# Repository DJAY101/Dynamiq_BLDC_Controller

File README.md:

# A simple Brushless Motor Controller

I'm currently on the journey of creating a simple cost effective controller that
will eventually be sold to the masses to remove the high barrier to entry into using high performing brushless motor actuators.

FRC Falcon 500 Motors inspired this project, since there are no suitable motor options at a suitable price that enables hobbyists to utilise these amazing pieces of technology. (Odrive being 200USD+)

# This project is still in its very early stages...
(Do note this is actually my very second PCB designed, so I lack a lot of experience)

Version 1 of the PCB worked with the following code. However I ended up frying two of the boards during programming and tinkering with the board. I am currently working on a version 2 iteration of the PCB from the mistakes and lack of safety features in V1. 

(I actually got the motor to turn on the very first iteration of this board which is a massive win)

## Failures so far...
- Somehow killed the TMC6200 gate driver while I was tinkering with the code. it does not like being fed a PWM duty cycle of greater than 40%
- Magic smoke occured on my buck converter where 4s Lipo is converted to 5V. Still unsure what happened here, but I have a few hypothesis. Sketchy soldering on my ESP32 3.3v and ground pin causing a short. Or accidentally shorting the the SPI clock pin with ground while unplugging the jumpers.
- The board does heat up, perhaps 2oZ layers may be needed (opted out since it was expensive for iter1)
- Practically no protection circuitry at all, except for the built in ones in the gate driver

# Improvements Underway
The progress on the code is halted as I have no working boards anymore since I fried all 2 of them haha.
- Integrate reverse polarity protection with a MOSFET Diode*
- Remove the chunky header pin and replace it with smaller header pins that connect to encoders and etc
- Initial inrush current limit to stop the spark when I connect my lipo to the board
- Fuses... Fuses and more fuses
- Change my LDO to a newer IC for more efficiency
- Capacitors on the phase output?
- Current sensing was not tested before the boards fried themselves ( caps on current sens outputs for a better averages value?)

# Other Unstructured Yap
PCB was manufactured by JLPCB, assembly services was also opted, 5 boards were 10 bucks aud and assembly and parts for 2 board added $150 aud

Reddit also reviewd my board before I manufactured it heres the link to that discussion
https://www.reddit.com/r/PCB/comments/1lk1n3d/review_request_my_first_pcb_bldc_sinusoidal/

This man made coding this thing a lot easier. Just pass sine waves into the motor and itll turn. I reckon it was much more easier to implement than step control.
https://www.youtube.com/watch?v=zSdetJsSeNw&t

Cool channels
- https://www.youtube.com/watch?v=mbJOxqxLkLE
- https://www.youtube.com/watch?v=e0sQnVmE7DU

If you'd like to contact me for more information or collaboration on this project feel free to DM me on insta at DJAY10101, or if you prefer email its djay01602@gmail.com

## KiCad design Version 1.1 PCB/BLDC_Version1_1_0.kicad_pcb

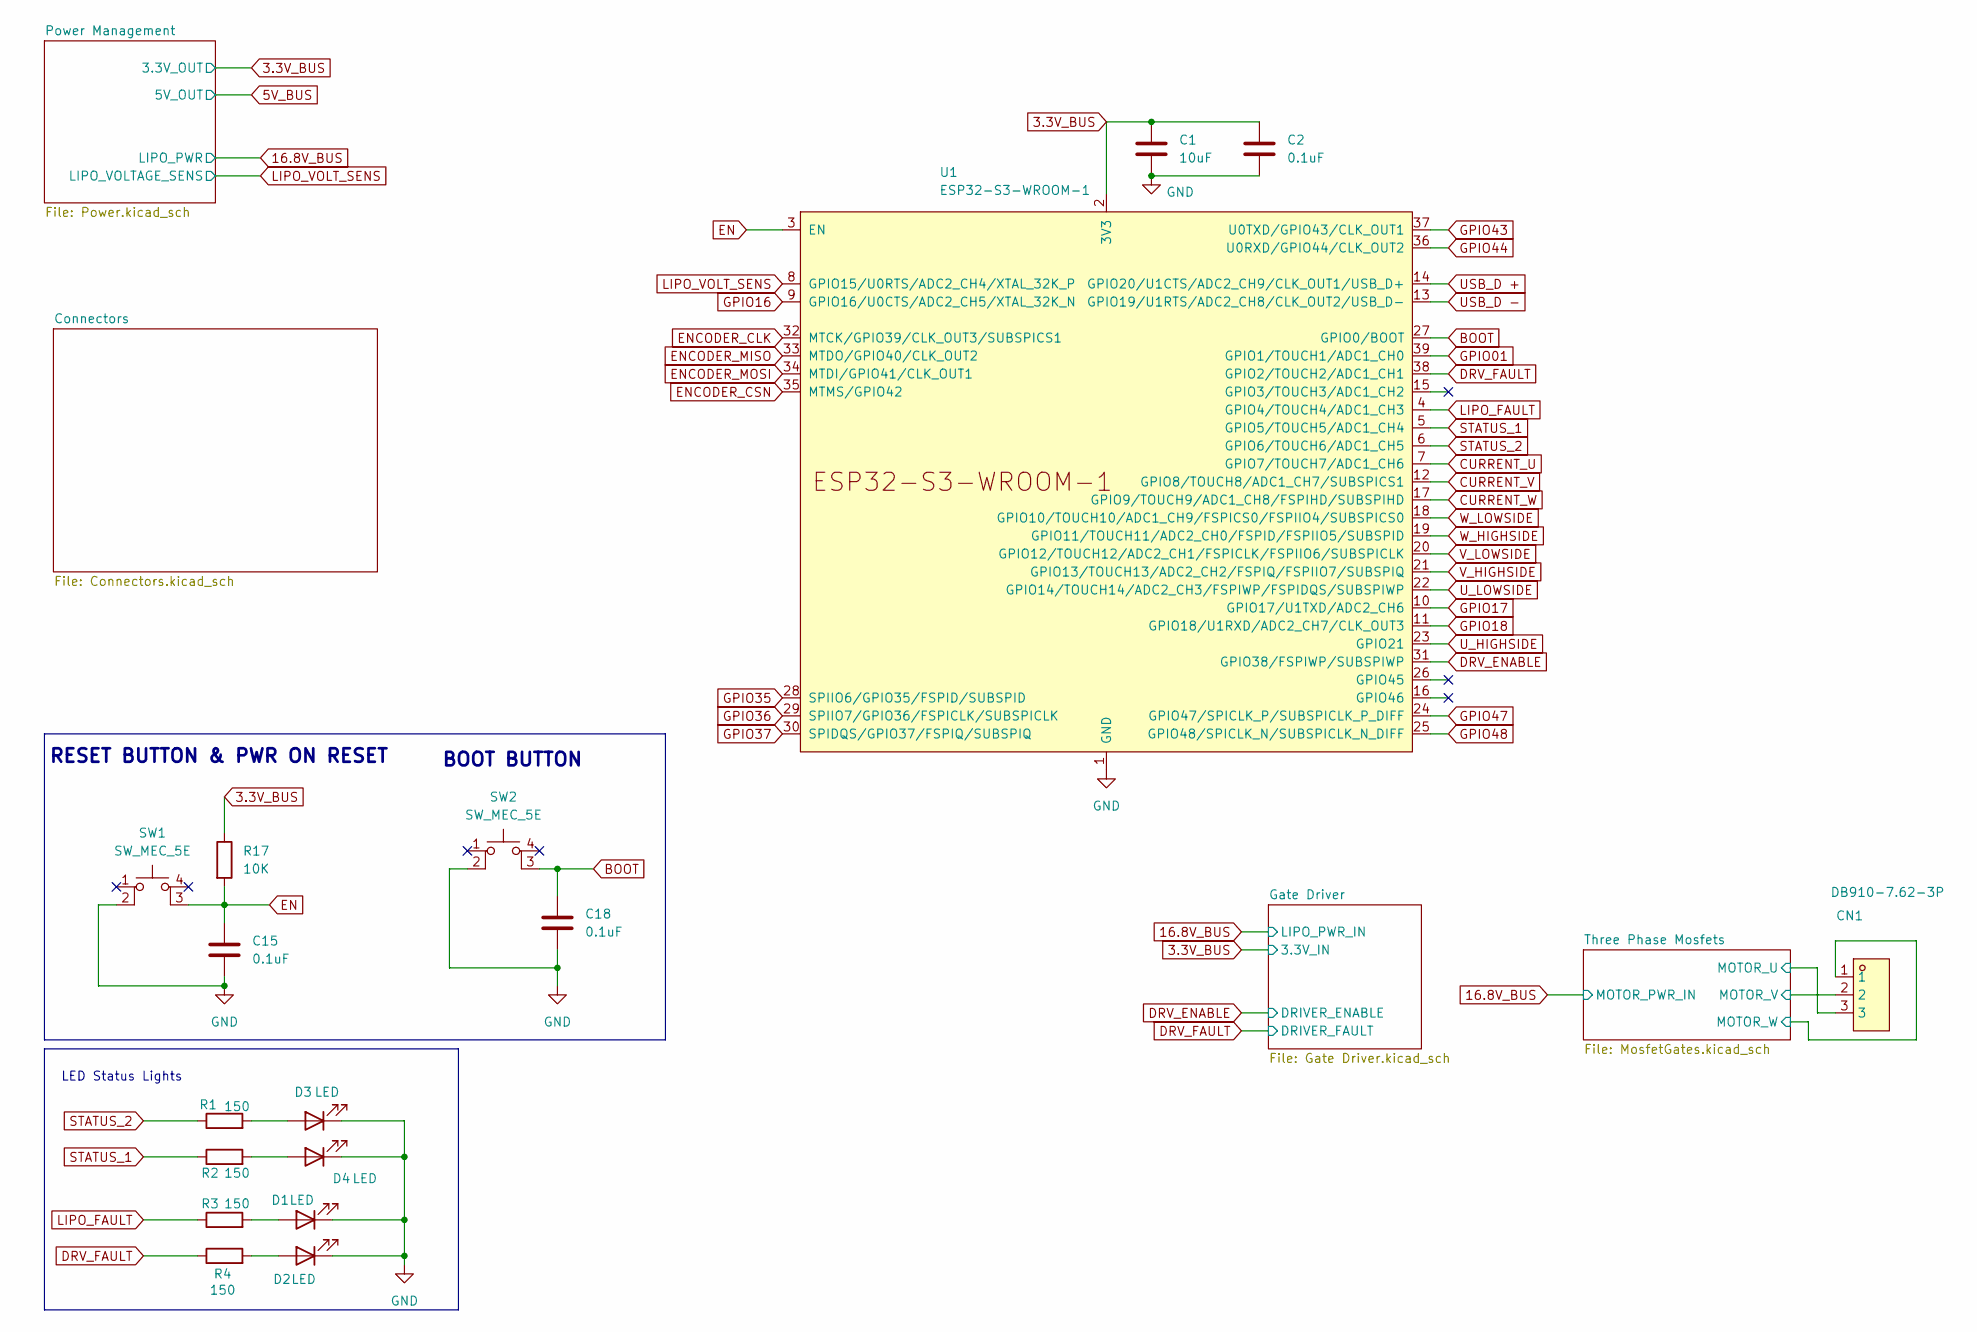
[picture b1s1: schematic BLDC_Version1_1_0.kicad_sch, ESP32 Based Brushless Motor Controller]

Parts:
C1: 10uF; C_0805_2012Metric_Pad1.18x1.45mm_HandSolder
C2, C15, C18: 0.1uF; C_0805_2012Metric_Pad1.18x1.45mm_HandSolder
CN1: DB910-7.62-3P; CONN-TH_3P-P7.62_DB910-7.62-3P; LCSC Part C395877
D1, D2: LED; LED_0603_1608Metric_Pad1.05x0.95mm_HandSolder
D3, D4: LED; LED_0805_2012Metric_Pad1.15x1.40mm_HandSolder
R1, R2, R3, R4: 150; R_0805_2012Metric_Pad1.20x1.40mm_HandSolder
R17: 10K; R_0805_2012Metric_Pad1.20x1.40mm_HandSolder
SW1, SW2: SW_MEC_5E; SW-SMD_4P-L5.2-W5.2-P3.70-LS6.5
U1: ESP32-S3-WROOM-1

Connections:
3.3V_BUS: C1.1, C2.1, R17.1, U1.2 (3V3); also elsewhere on the board
BOOT: C18.1, SW2.3 (K), U1.27 (GPIO0/BOOT)
CURRENT_U: U1.7 (GPIO7/TOUCH7/ADC1_CH6); also elsewhere on the board
CURRENT_V: U1.12 (GPIO8/TOUCH8/ADC1_CH7/SUBSPICS1); also elsewhere on the board
CURRENT_W: U1.17 (GPIO9/TOUCH9/ADC1_CH8/FSPIHD/SUBSPIHD); also elsewhere on the board
DRV_ENABLE: U1.31 (GPIO38/FSPIWP/SUBSPIWP); also elsewhere on the board
DRV_FAULT: R4.1, U1.38 (GPIO2/TOUCH2/ADC1_CH1); also elsewhere on the board
EN: C15.1, R17.2, SW1.3 (K), U1.3 (EN)
ENCODER_CLK: U1.32 (MTCK/GPIO39/CLK_OUT3/SUBSPICS1); also elsewhere on the board
ENCODER_CSN: U1.35 (MTMS/GPIO42); also elsewhere on the board
ENCODER_MISO: U1.33 (MTDO/GPIO40/CLK_OUT2); also elsewhere on the board
ENCODER_MOSI: U1.34 (MTDI/GPIO41/CLK_OUT1); also elsewhere on the board
GND: C1.2, C2.2, C15.2, C18.2, D1.1 (K), D2.1 (K), D3.1 (K), D4.1 (K), SW1.2, SW2.2, U1.1 (GND), U1.40 (GND), U1.41 (GND); also elsewhere on the board
GPIO01: U1.39 (GPIO1/TOUCH1/ADC1_CH0); also elsewhere on the board
GPIO16: U1.9 (GPIO16/U0CTS/ADC2_CH5/XTAL_32K_N); also elsewhere on the board
GPIO17: U1.10 (GPIO17/U1TXD/ADC2_CH6); also elsewhere on the board
GPIO18: U1.11 (GPIO18/U1RXD/ADC2_CH7/CLK_OUT3); also elsewhere on the board
GPIO35: U1.28 (SPIIO6/GPIO35/FSPID/SUBSPID); also elsewhere on the board
GPIO36: U1.29 (SPIIO7/GPIO36/FSPICLK/SUBSPICLK); also elsewhere on the board
GPIO37: U1.30 (SPIDQS/GPIO37/FSPIQ/SUBSPIQ); also elsewhere on the board
GPIO43: U1.37 (U0TXD/GPIO43/CLK_OUT1); also elsewhere on the board
GPIO44: U1.36 (U0RXD/GPIO44/CLK_OUT2); also elsewhere on the board
GPIO47: U1.24 (GPIO47/SPICLK_P/SUBSPICLK_P_DIFF); also elsewhere on the board
GPIO48: U1.25 (GPIO48/SPICLK_N/SUBSPICLK_N_DIFF); also elsewhere on the board
LIPO_FAULT: R3.1, U1.4 (GPIO4/TOUCH4/ADC1_CH3)
LIPO_VOLT_SENS: U1.8 (GPIO15/U0RTS/ADC2_CH4/XTAL_32K_P); also elsewhere on the board
unnamed: D1.2 (A), R3.2
unnamed: D2.2 (A), R4.2
unnamed: D3.2 (A), R1.2
unnamed: D4.2 (A), R2.2
STATUS_1: R2.1, U1.5 (GPIO5/TOUCH5/ADC1_CH4)
STATUS_2: R1.1, U1.6 (GPIO6/TOUCH6/ADC1_CH5)
U_HIGHSIDE: U1.23 (GPIO21); also elsewhere on the board
U_LOWSIDE: U1.22 (GPIO14/TOUCH14/ADC2_CH3/FSPIWP/FSPIDQS/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); also elsewhere on the board
U_SENSE: CN1.3; also elsewhere on the board
V_HIGHSIDE: U1.21 (GPIO13/TOUCH13/ADC2_CH2/FSPIQ/FSPIIO7/S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); also elsewhere on the board
V_LOWSIDE: U1.20 (GPIO12/TOUCH12/ADC2_CH1/FSPICLK/FSPIIO6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); also elsewhere on the board
V_SENSE: CN1.2; also elsewhere on the board
W_HIGHSIDE: U1.19 (GPIO11/TOUCH11/ADC2_CH0/FSPID/FSPIIO5/S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); also elsewhere on the board
W_LOWSIDE: U1.18 (GPIO10/TOUCH10/ADC1_CH9/FSPICS0/FSPIIO4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); also elsewhere on the board
W_SENSE: CN1.1; also elsewhere on the board

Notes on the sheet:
RESET BUTTON & PWR ON RESET
BOOT BUTTON
LED Status Lights

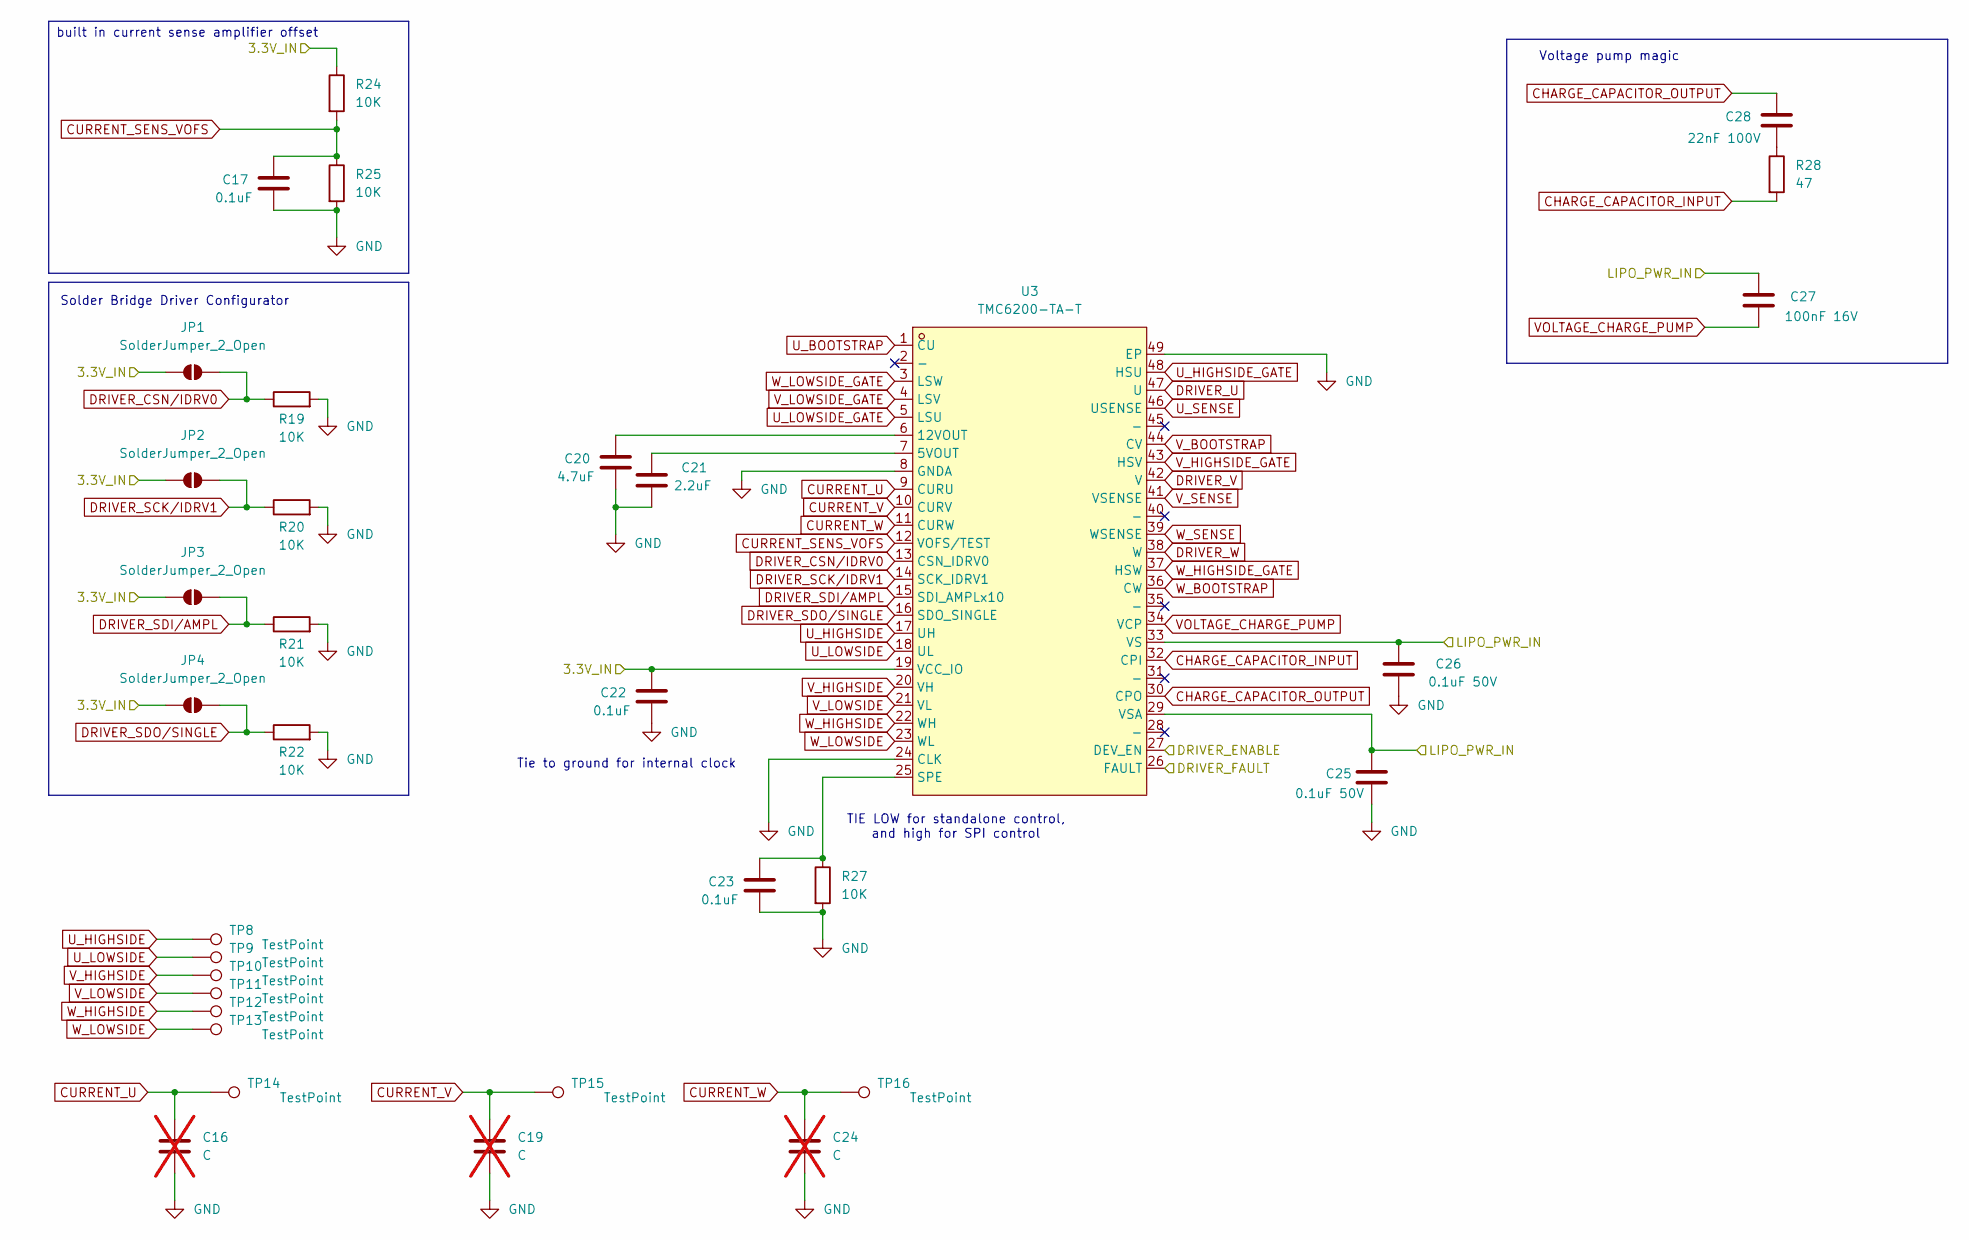
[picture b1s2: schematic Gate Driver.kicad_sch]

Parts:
C16, C19, C24: C; C_0805_2012Metric_Pad1.18x1.45mm_HandSolder; not fitted
C17, C22, C23: 0.1uF; C_0805_2012Metric_Pad1.18x1.45mm_HandSolder
C20: 4.7uF; C_0805_2012Metric_Pad1.18x1.45mm_HandSolder
C21: 2.2uF; C_0805_2012Metric_Pad1.18x1.45mm_HandSolder
C25, C26: 0.1uF 50V; C_0805_2012Metric_Pad1.18x1.45mm_HandSolder
C27: 100nF 16V; C_0805_2012Metric_Pad1.18x1.45mm_HandSolder
C28: 22nF 100V; C_0805_2012Metric_Pad1.18x1.45mm_HandSolder
JP1, JP2, JP3, JP4: SolderJumper_2_Open; SolderJumper-2_P1.3mm_Open_TrianglePad1.0x1.5mm
R19, R20, R21, R22, R24, R25, R27: 10K; R_0805_2012Metric_Pad1.20x1.40mm_HandSolder
R28: 47; R_0805_2012Metric_Pad1.20x1.40mm_HandSolder
TP8, TP9, TP10, TP11, TP12, TP13: TestPoint; TestPoint_Pad_D2.0mm
TP14, TP15, TP16: TestPoint; SMD_RH-5015
U3: TMC6200-TA-T; TQFP-48_L7.0-W7.0-P0.50-LS9.0-BL-EP; LCSC Part C465958

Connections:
3.3V_BUS: C22.1, JP1.1 (A), JP2.1 (A), JP3.1 (A), JP4.1 (A), R24.1, U3.19 (VCC_IO); also elsewhere on the board
16.8V_BUS: C25.1, C26.1, C27.1, U3.29 (VSA), U3.33 (VS); also elsewhere on the board
CHARGE_CAPACITOR_INPUT: R28.2, U3.32 (CPI)
CHARGE_CAPACITOR_OUTPUT: C28.1, U3.30 (CPO)
CURRENT_SENS_VOFS: C17.1, R24.2, R25.1, U3.12 (VOFS/TEST)
CURRENT_U: C16.1, TP14.1, U3.9 (CURU); also elsewhere on the board
CURRENT_V: C19.1, TP15.1, U3.10 (CURV); also elsewhere on the board
CURRENT_W: C24.1, TP16.1, U3.11 (CURW); also elsewhere on the board
DRIVER_CSN/IDRV0: JP1.2 (B), R19.1, U3.13 (CSN_IDRV0); also elsewhere on the board
DRIVER_SCK/IDRV1: JP2.2 (B), R20.1, U3.14 (SCK_IDRV1); also elsewhere on the board
DRIVER_SDI/AMPL: JP3.2 (B), R21.1, U3.15 (SDI_AMPLx10); also elsewhere on the board
DRIVER_SDO/SINGLE: JP4.2 (B), R22.1, U3.16 (SDO_SINGLE); also elsewhere on the board
DRIVER_U: U3.47 (U); also elsewhere on the board
DRIVER_V: U3.42 (V); also elsewhere on the board
DRIVER_W: U3.38 (W); also elsewhere on the board
DRV_ENABLE: U3.27 (DEV_EN); also elsewhere on the board
DRV_FAULT: U3.26 (FAULT); also elsewhere on the board
GND: C16.2, C17.2, C19.2, C20.2, C21.2, C22.2, C23.2, C24.2, C25.2, C26.2, R19.2, R20.2, R21.2, R22.2, R25.2, R27.2, U3.8 (GNDA), U3.24 (CLK), U3.49 (EP); also elsewhere on the board
unnamed: C28.2, R28.1
unnamed: C21.1, U3.7 (5VOUT)
unnamed: C20.1, U3.6 (12VOUT)
unnamed: C23.1, R27.1, U3.25 (SPE)
U_BOOTSTRAP: U3.1 (CU); also elsewhere on the board
U_HIGHSIDE: TP8.1, U3.17 (UH); also elsewhere on the board
U_HIGHSIDE_GATE: U3.48 (HSU); also elsewhere on the board
U_LOWSIDE: TP9.1, U3.18 (UL); also elsewhere on the board
U_LOWSIDE_GATE: U3.5 (LSU); also elsewhere on the board
U_SENSE: U3.46 (USENSE); also elsewhere on the board
VOLTAGE_CHARGE_PUMP: C27.2, U3.34 (VCP)
V_BOOTSTRAP: U3.44 (CV); also elsewhere on the board
V_HIGHSIDE: TP10.1, U3.20 (VH); also elsewhere on the board
V_HIGHSIDE_GATE: U3.43 (HSV); also elsewhere on the board
V_LOWSIDE: TP11.1, U3.21 (VL); also elsewhere on the board
V_LOWSIDE_GATE: U3.4 (LSV); also elsewhere on the board
V_SENSE: U3.41 (VSENSE); also elsewhere on the board
W_BOOTSTRAP: U3.36 (CW); also elsewhere on the board
W_HIGHSIDE: TP12.1, U3.22 (WH); also elsewhere on the board
W_HIGHSIDE_GATE: U3.37 (HSW); also elsewhere on the board
W_LOWSIDE: TP13.1, U3.23 (WL); also elsewhere on the board
W_LOWSIDE_GATE: U3.3 (LSW); also elsewhere on the board
W_SENSE: U3.39 (WSENSE); also elsewhere on the board

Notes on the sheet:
built in current sense amplifier offset
Voltage pump magic
Tie to ground for internal clock
Solder Bridge Driver Configurator
TIE LOW for standalone control, and high for SPI control

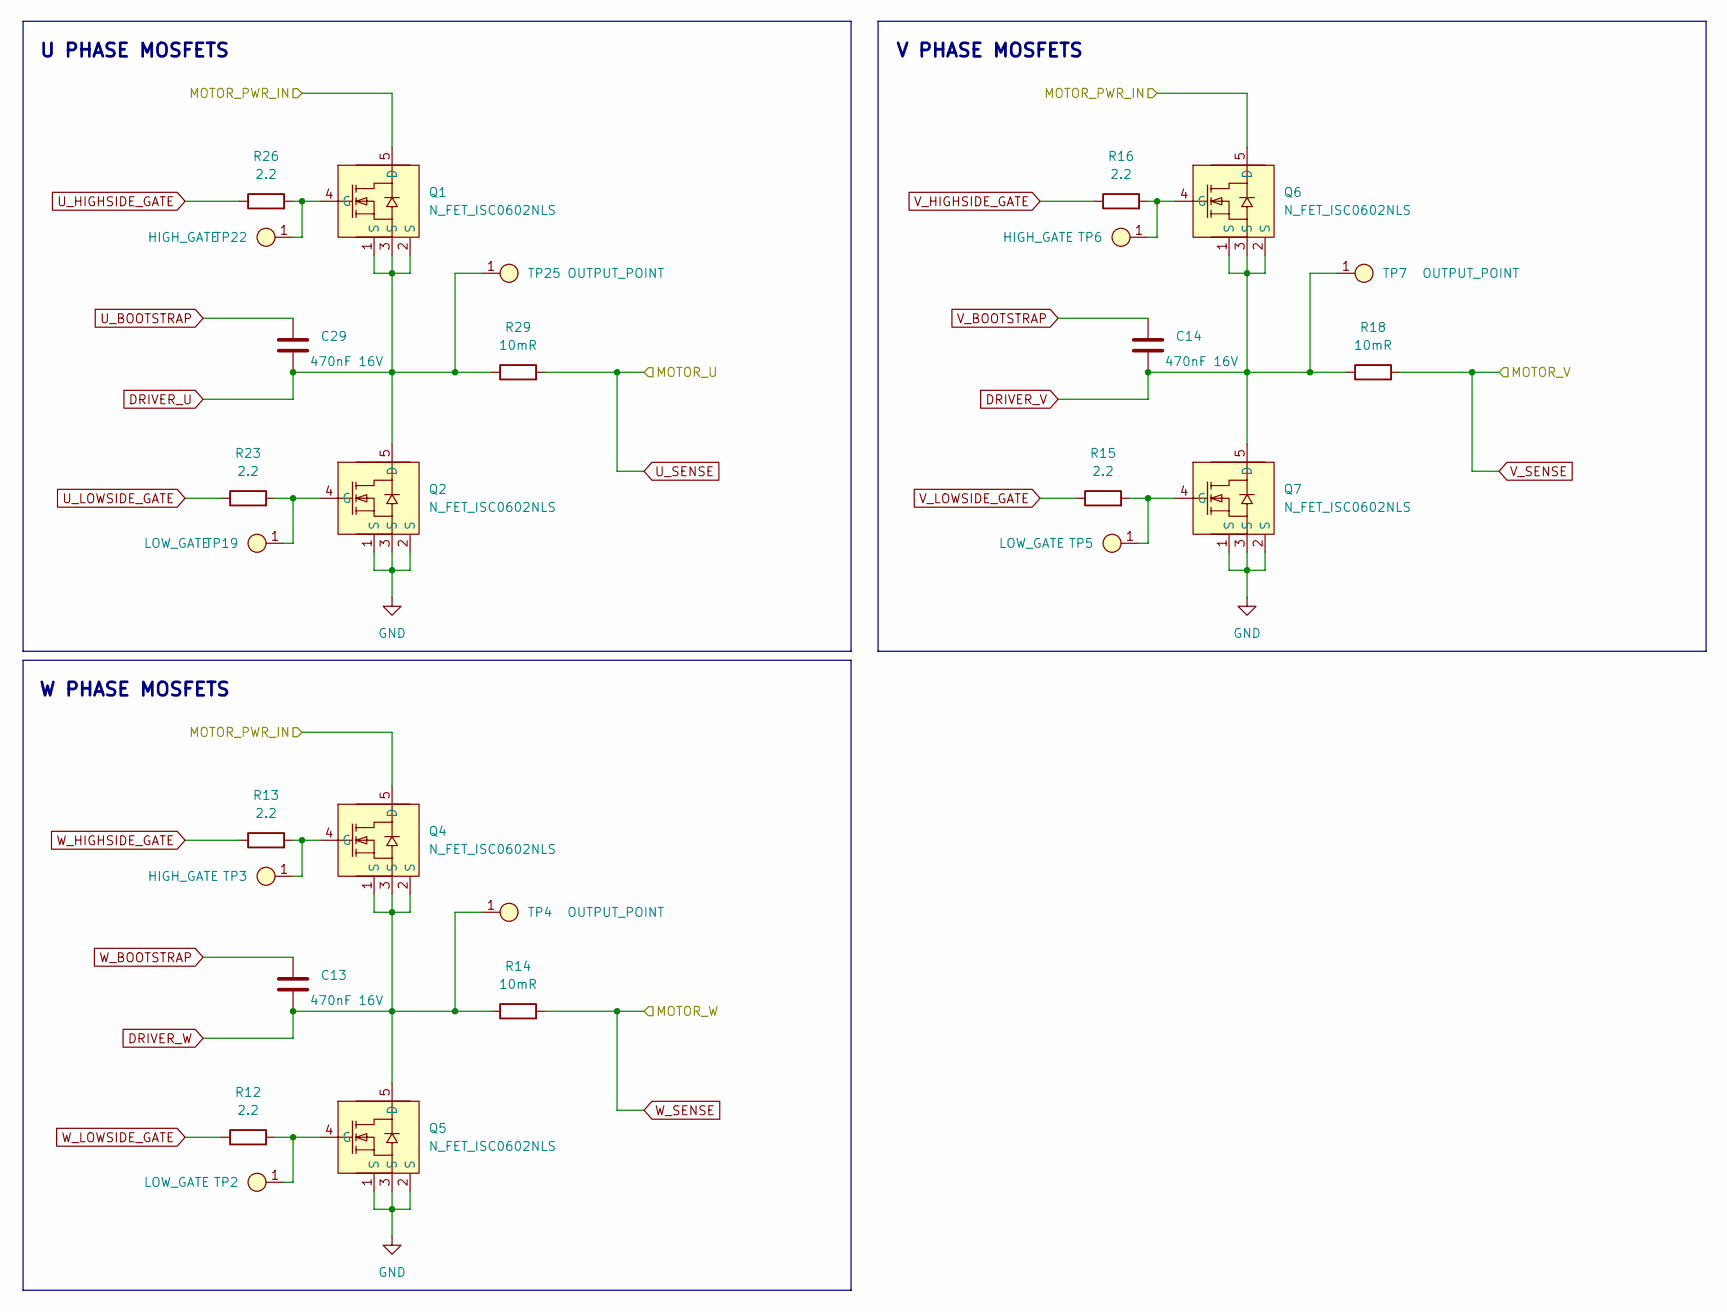
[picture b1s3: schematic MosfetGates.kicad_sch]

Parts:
C13, C14, C29: 470nF 16V; C_0805_2012Metric_Pad1.18x1.45mm_HandSolder
Q1, Q2, Q4, Q5, Q6, Q7: N_FET_ISC0602NLS; Infineon_PG-TDSON-8_6.15x5.15mm
R12, R13, R15, R16, R23, R26: 2.2; R_0805_2012Metric_Pad1.20x1.40mm_HandSolder
R14, R18, R29: 10mR; R_2512_6332Metric_Pad1.40x3.35mm_HandSolder
TP2, TP5, TP19: LOW_GATE; SMD_RH-5015
TP3, TP6, TP22: HIGH_GATE; SMD_RH-5015
TP4, TP7, TP25: OUTPUT_POINT; SMD_RH-5015

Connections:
16.8V_BUS: Q1.5 (D), Q4.5 (D), Q6.5 (D); also elsewhere on the board
DRIVER_U: C29.2, Q1.1 (S), Q1.2 (S), Q1.3 (S), Q2.5 (D), R29.1, TP25.1; also elsewhere on the board
DRIVER_V: C14.2, Q6.1 (S), Q6.2 (S), Q6.3 (S), Q7.5 (D), R18.1, TP7.1; also elsewhere on the board
DRIVER_W: C13.2, Q4.1 (S), Q4.2 (S), Q4.3 (S), Q5.5 (D), R14.1, TP4.1; also elsewhere on the board
GND: Q2.1 (S), Q2.2 (S), Q2.3 (S), Q5.1 (S), Q5.2 (S), Q5.3 (S), Q7.1 (S), Q7.2 (S), Q7.3 (S); also elsewhere on the board
unnamed: Q1.4 (G), R26.2, TP22.1
unnamed: Q2.4 (G), R23.2, TP19.1
unnamed: Q4.4 (G), R13.2, TP3.1
unnamed: Q5.4 (G), R12.2, TP2.1
unnamed: Q6.4 (G), R16.2, TP6.1
unnamed: Q7.4 (G), R15.2, TP5.1
U_BOOTSTRAP: C29.1; also elsewhere on the board
U_HIGHSIDE_GATE: R26.1; also elsewhere on the board
U_LOWSIDE_GATE: R23.1; also elsewhere on the board
U_SENSE: R29.2; also elsewhere on the board
V_BOOTSTRAP: C14.1; also elsewhere on the board
V_HIGHSIDE_GATE: R16.1; also elsewhere on the board
V_LOWSIDE_GATE: R15.1; also elsewhere on the board
V_SENSE: R18.2; also elsewhere on the board
W_BOOTSTRAP: C13.1; also elsewhere on the board
W_HIGHSIDE_GATE: R13.1; also elsewhere on the board
W_LOWSIDE_GATE: R12.1; also elsewhere on the board
W_SENSE: R14.2; also elsewhere on the board

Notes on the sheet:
U PHASE MOSFETS
V PHASE MOSFETS
W PHASE MOSFETS

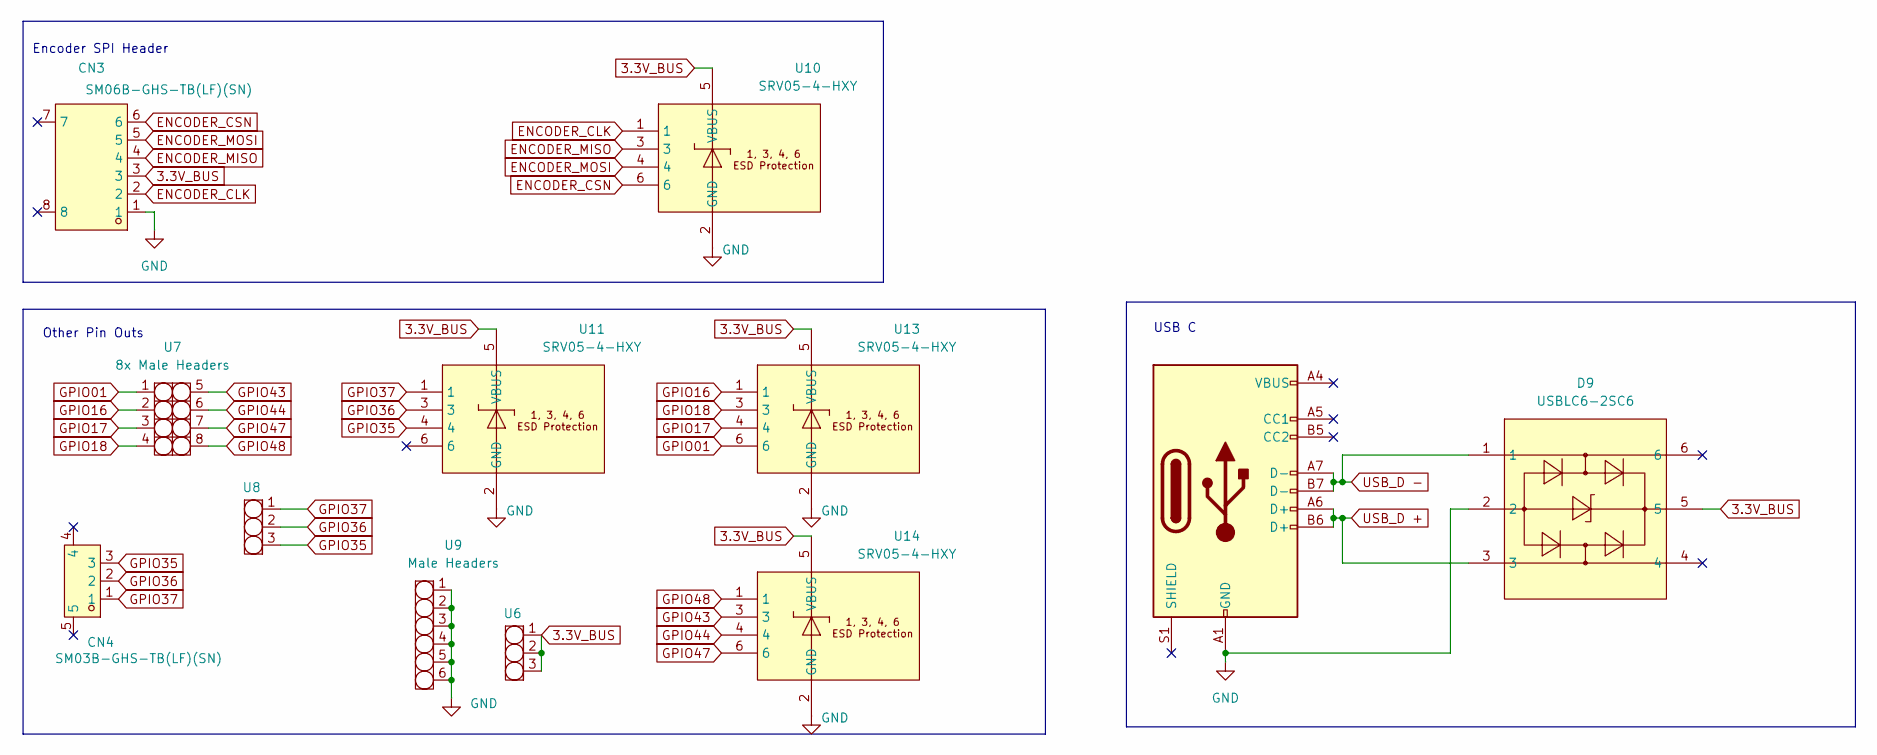
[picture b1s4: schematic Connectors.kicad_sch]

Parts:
CN3: SM06B-GHS-TB(LF)(SN); CONN-TH_SM06B-GHS-TB-LF-SN; LCSC Part C133065
CN4: SM03B-GHS-TB(LF)(SN); CONN-TH_SM03B-GHS-TB-LF-SN; LCSC Part C514175
D9: USBLC6-2SC6; SOT-23-6_L2.9-W1.6-P0.95-LS2.8-BL; LCSC Part C7519
J1: USB_C_Receptacle_USB2.0_14P; USB-C_SMD-TYPE-C-31-M-12
U6, U8: 1x3 Male Headers
U7: 8x Male Headers; 2x4 Male Headers
U9: Male Headers; 1x6 Male Headers
U10, U11, U13, U14: SRV05-4-HXY; SOT-23-6_L2.9-W1.6-P0.95-LS2.8-BR; LCSC Part C4748793

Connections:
3.3V_BUS: CN3.3, D9.5, U6.1, U6.2, U6.3, U10.5 (VBUS), U11.5 (VBUS), U13.5 (VBUS), U14.5 (VBUS); also elsewhere on the board
ENCODER_CLK: CN3.2, U10.1; also elsewhere on the board
ENCODER_CSN: CN3.6, U10.6; also elsewhere on the board
ENCODER_MISO: CN3.4, U10.3; also elsewhere on the board
ENCODER_MOSI: CN3.5, U10.4; also elsewhere on the board
GND: CN3.1, D9.2, J1.A1 (GND), J1.A12 (GND), J1.B1 (GND), J1.B12 (GND), U9.1, U9.2, U9.3, U9.4, U9.5, U9.6, U10.2 (GND), U11.2 (GND), U13.2 (GND), U14.2 (GND); also elsewhere on the board
GPIO01: U7.1, U13.6; also elsewhere on the board
GPIO16: U7.2, U13.1; also elsewhere on the board
GPIO17: U7.3, U13.4; also elsewhere on the board
GPIO18: U7.4, U13.3; also elsewhere on the board
GPIO35: CN4.3, U8.3, U11.4; also elsewhere on the board
GPIO36: CN4.2, U8.2, U11.3; also elsewhere on the board
GPIO37: CN4.1, U8.1, U11.1; also elsewhere on the board
GPIO43: U7.5, U14.3; also elsewhere on the board
GPIO44: U7.6, U14.4; also elsewhere on the board
GPIO47: U7.7, U14.6; also elsewhere on the board
GPIO48: U7.8, U14.1; also elsewhere on the board

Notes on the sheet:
USB C
Encoder SPI Header
Other Pin Outs

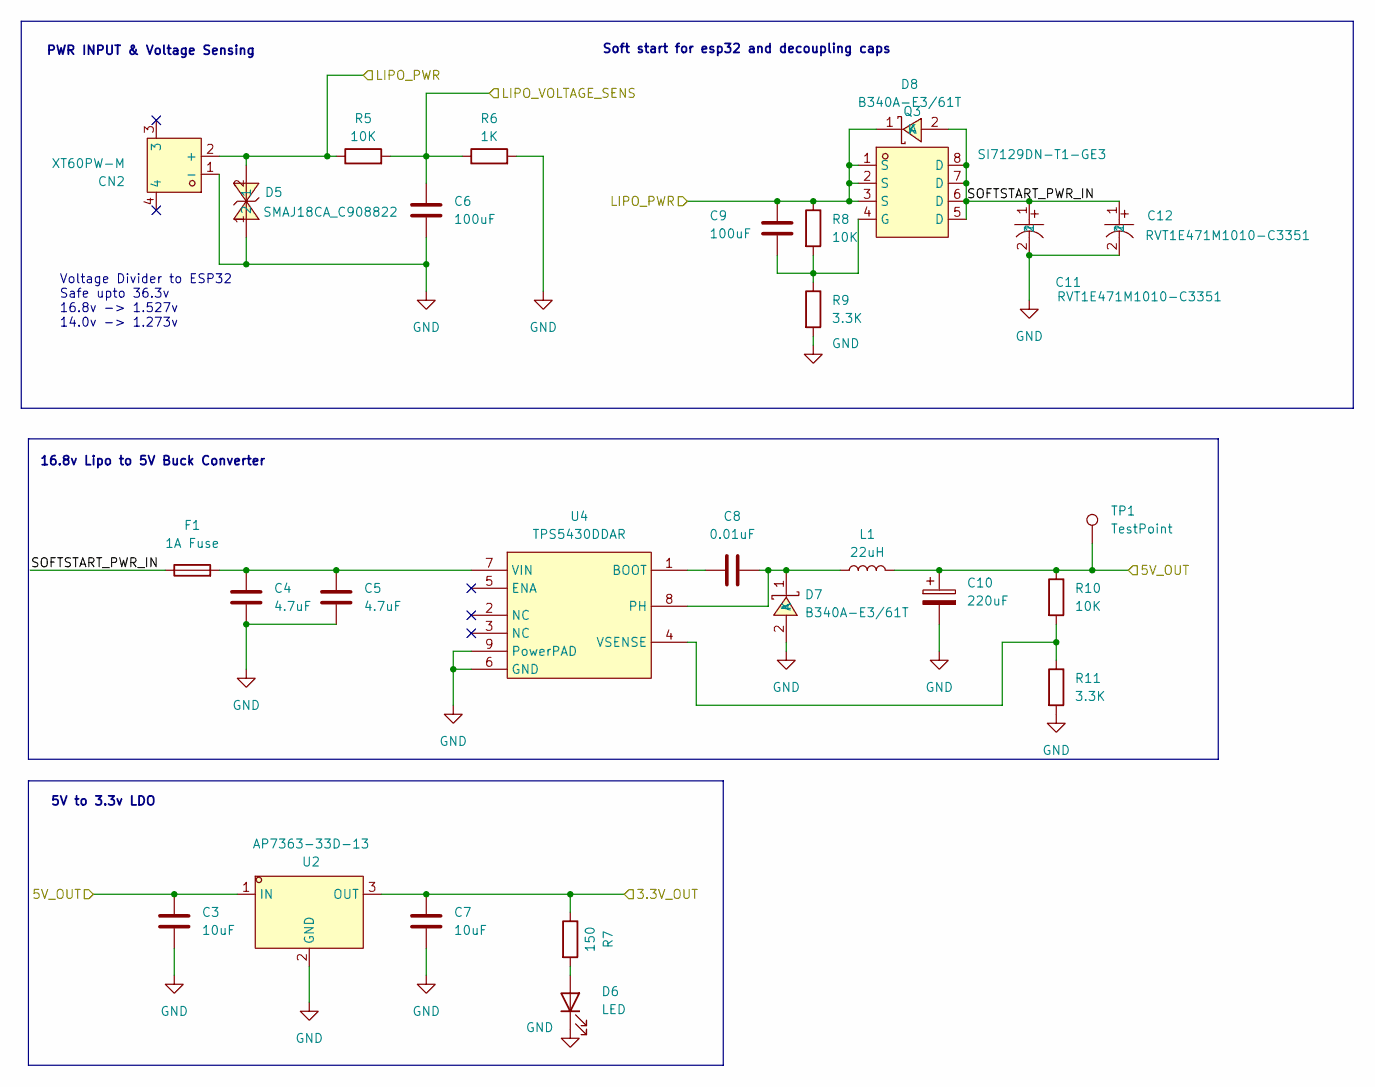
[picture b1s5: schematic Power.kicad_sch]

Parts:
C3, C7: 10uF; C_0805_2012Metric_Pad1.18x1.45mm_HandSolder
C4, C5: 4.7uF; C_0805_2012Metric_Pad1.18x1.45mm_HandSolder
C6, C9: 100uF; C_0805_2012Metric_Pad1.18x1.45mm_HandSolder
C8: 0.01uF; C_0805_2012Metric_Pad1.18x1.45mm_HandSolder
C10: 220uF; C_0805_2012Metric_Pad1.18x1.45mm_HandSolder
C11, C12: RVT1E471M1010-C3351; CAP-SMD_BD10.0-L10.3-W10.3-LS11.0-FD; LCSC Part C3351
CN2: XT60PW-M; CONN-TH_XT60PW-M; LCSC Part C98732
D5: SMAJ18CA_C908822; SMA_L4.4-W2.8-LS5.1-BI; LCSC Part C908822
D6: LED; LED_0805_2012Metric_Pad1.15x1.40mm_HandSolder
D7, D8: B340A-E3/61T; SMA_L4.3-W2.6-LS5.2-RD; LCSC Part C15570
F1: 1A Fuse; Fuse_1206_3216Metric_Pad1.42x1.75mm_HandSolder
L1: 22uH; IND-SMD_L5.5-W5.2
Q3: SI7129DN-T1-GE3; POWERPAK-1212-8_L3.3-W3.3-P0.65-BL-EP; LCSC Part C727679
R5, R8, R10: 10K; R_0805_2012Metric_Pad1.20x1.40mm_HandSolder
R6: 1K; R_0805_2012Metric_Pad1.20x1.40mm_HandSolder
R7: 150; R_0805_2012Metric_Pad1.20x1.40mm_HandSolder
R9, R11: 3.3K; R_0805_2012Metric_Pad1.20x1.40mm_HandSolder
TP1: TestPoint; TestPoint_Pad_D3.0mm
U2: AP7363-33D-13; DPAK-3_L6.6-W6.1-P2.28-LS9.9-BR; LCSC Part C108723
U4: TPS5430DDAR; ESOP-8_L4.9-W3.9-P1.27-LS6.0-TL-EP; LCSC Part C9864

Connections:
3.3V_BUS: C7.1, R7.1, U2.3 (OUT); also elsewhere on the board
5V_BUS: C3.1, C10.1, L1.2, R10.1, TP1.1, U2.1 (IN); also elsewhere on the board
16.8V_BUS: C9.2, CN2.2 (+), D5.2, D8.1 (K), Q3.1 (S), Q3.2 (S), Q3.3 (S), R5.1, R8.1; also elsewhere on the board
/Power Management/SOFTSTART_PWR_IN: C11.1, C12.1, D8.2 (A), F1.1, Q3.5 (D), Q3.6 (D), Q3.7 (D), Q3.8 (D)
GND: C3.2, C4.2, C5.2, C6.2, C7.2, C10.2, C11.2, C12.2, CN2.1 (-), D5.1, D6.1 (K), D7.2 (A), R6.2, R9.2, R11.2, U2.2 (GND), U4.6 (GND), U4.9 (PowerPAD); also elsewhere on the board
LIPO_VOLT_SENS: C6.1, R5.2, R6.1; also elsewhere on the board
unnamed: D6.2 (A), R7.2
unnamed: C8.2, D7.1 (K), L1.1, U4.8 (PH)
unnamed: C9.1, Q3.4 (G), R8.2, R9.1
unnamed: C8.1, U4.1 (BOOT)
unnamed: C4.1, C5.1, F1.2, U4.7 (VIN)
unnamed: R10.2, R11.1, U4.4 (VSENSE)

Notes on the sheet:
Voltage Divider to ESP32 Safe upto 36.3v 16.8v -> 1.527v 14.0v -> 1.273v
PWR INPUT & Voltage Sensing
16.8v Lipo to 5V Buck Converter
5V to 3.3v LDO
Soft start for esp32 and decoupling caps

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
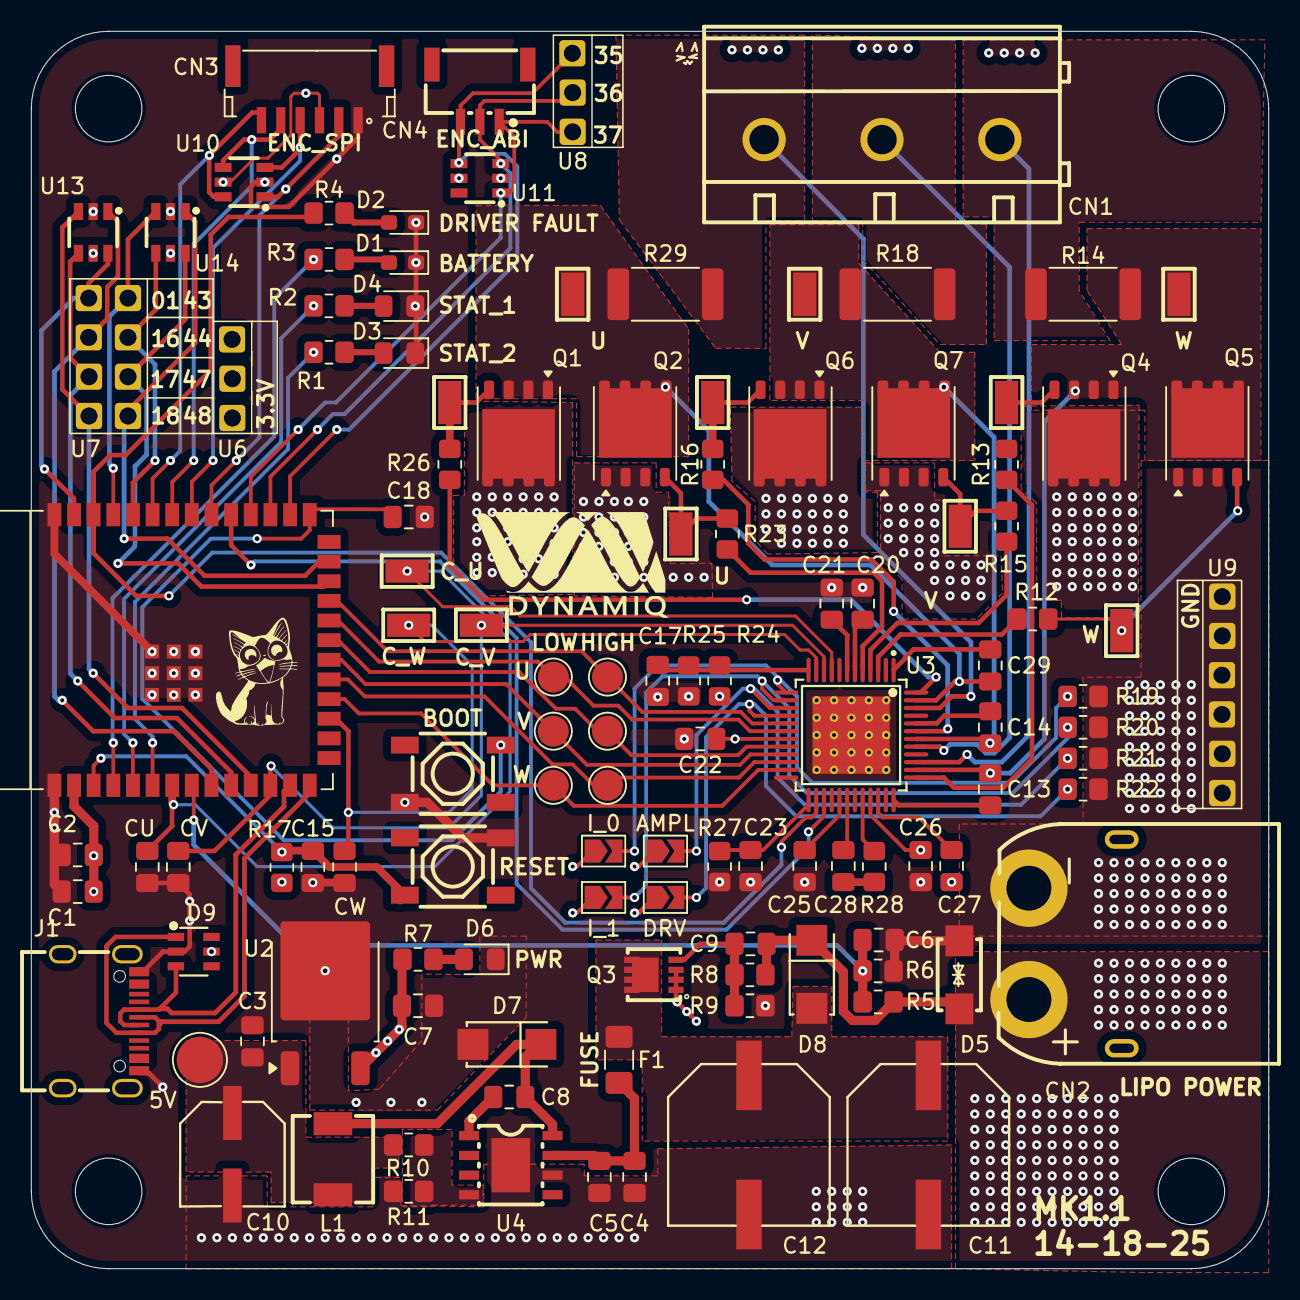
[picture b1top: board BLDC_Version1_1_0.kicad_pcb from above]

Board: 4 copper layers, 80.0 x 80.0 mm, 118 parts (0 on the bottom side), 82 nets.

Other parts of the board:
5V: TestPoint; TestPoint_Pad_D3.0mm
AMPL: SolderJumper_2_Open; SolderJumper-2_P1.3mm_Open_TrianglePad1.0x1.5mm
CU: C; C_0805_2012Metric_Pad1.18x1.45mm_HandSolder
CV: C; C_0805_2012Metric_Pad1.18x1.45mm_HandSolder
CW: C; C_0805_2012Metric_Pad1.18x1.45mm_HandSolder
DRV: SolderJumper_2_Open; SolderJumper-2_P1.3mm_Open_TrianglePad1.0x1.5mm
I_0, I_1: SolderJumper_2_Open; SolderJumper-2_P1.3mm_Open_TrianglePad1.0x1.5mm

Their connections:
3.3V_BUS: AMPL.1 (A), DRV.1 (A), I_0.1 (A), I_1.1 (A); also elsewhere on the board
5V_BUS: 5V.1; also elsewhere on the board
CURRENT_U: CU.1; also elsewhere on the board
CURRENT_V: CV.1; also elsewhere on the board
CURRENT_W: CW.1; also elsewhere on the board
DRIVER_CSN/IDRV0: I_0.2 (B); also elsewhere on the board
DRIVER_SCK/IDRV1: I_1.2 (B); also elsewhere on the board
DRIVER_SDI/AMPL: AMPL.2 (B); also elsewhere on the board
DRIVER_SDO/SINGLE: DRV.2 (B); also elsewhere on the board
GND: CU.2, CV.2, CW.2; also elsewhere on the board

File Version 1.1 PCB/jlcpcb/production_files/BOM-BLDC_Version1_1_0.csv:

Comment,Designator,Footprint,LCSC,Quantity
SW_MEC_5E,"SW1,SW2",SW-SMD_4P-L5.2-W5.2-P3.70-LS6.5,C10852,2
SM06B-GHS-TB(LF)(SN),CN3,CONN-TH_SM06B-GHS-TB-LF-SN,C133065,1
470nF 16V,"C13,C14,C29",C_0805_2012Metric_Pad1.18x1.45mm_HandSolder,C13967,3
100uF,"C6,C9",C_0805_2012Metric_Pad1.18x1.45mm_HandSolder,C141660,2
10uF,"C1,C3,C7",C_0805_2012Metric_Pad1.18x1.45mm_HandSolder,C15850,3
USB_C_Receptacle_USB2.0_14P,J1,USB-C_SMD-TYPE-C-31-M-12,C165948,1
0.01uF,C8,C_0805_2012Metric_Pad1.18x1.45mm_HandSolder,C1710,1
10K,"R10,R17,R19,R20,R21,R22,R24,R25,R27,R5,R8",R_0805_2012Metric_Pad1.20x1.40mm_HandSolder,C17414,11
150,"R1,R2,R3,R4,R7",R_0805_2012Metric_Pad1.20x1.40mm_HandSolder,C17471,5
1K,R6,R_0805_2012Metric_Pad1.20x1.40mm_HandSolder,C17513,1
2.2,"R12,R13,R15,R16,R23,R26",R_0805_2012Metric_Pad1.20x1.40mm_HandSolder,C17521,6
47,R28,R_0805_2012Metric_Pad1.20x1.40mm_HandSolder,C17714,1
4.7uF,"C20,C4,C5",C_0805_2012Metric_Pad1.18x1.45mm_HandSolder,C1779,3
LED,"D1,D2",LED_0603_1608Metric_Pad1.05x0.95mm_HandSolder,C2286,2
LED,D3,LED_0805_2012Metric_Pad1.15x1.40mm_HandSolder,C2296,1
LED,"D4,D6",LED_0805_2012Metric_Pad1.15x1.40mm_HandSolder,C2297,2
3.3K,"R11,R9",R_0805_2012Metric_Pad1.20x1.40mm_HandSolder,C26010,2
0.1uF,"C15,C17,C18,C2,C22,C23,C25,C26,C27",C_0805_2012Metric_Pad1.18x1.45mm_HandSolder,C28233,9
2.2uF,C21,C_0805_2012Metric_Pad1.18x1.45mm_HandSolder,C377773,1
DB910-7.62-3P,CN1,CONN-TH_3P-P7.62_DB910-7.62-3P,C395877,1
SRV05-4-HXY,"U10,U11,U13,U14",SOT-23-6_L2.9-W1.6-P0.95-LS2.8-BR,C4748793,4
SM03B-GHS-TB(LF)(SN),CN4,CONN-TH_SM03B-GHS-TB-LF-SN,C514175,1
TestPoint,"TP14,TP15,TP16,TP19,TP2,TP22,TP25,TP3,TP4,TP5,TP6,TP7",SMD_RH-5015,C5199798,12
22nF 100V,C28,C_0805_2012Metric_Pad1.18x1.45mm_HandSolder,C61998,1
USBLC6-2SC6,D9,SOT-23-6_L2.9-W1.6-P0.95-LS2.8-BL,C7519,1
TPS5430DDAR,U4,ESOP-8_L4.9-W3.9-P1.27-LS6.0-TL-EP,C9864,1
XT60PW-M,CN2,CONN-TH_XT60PW-M,C98732,1
